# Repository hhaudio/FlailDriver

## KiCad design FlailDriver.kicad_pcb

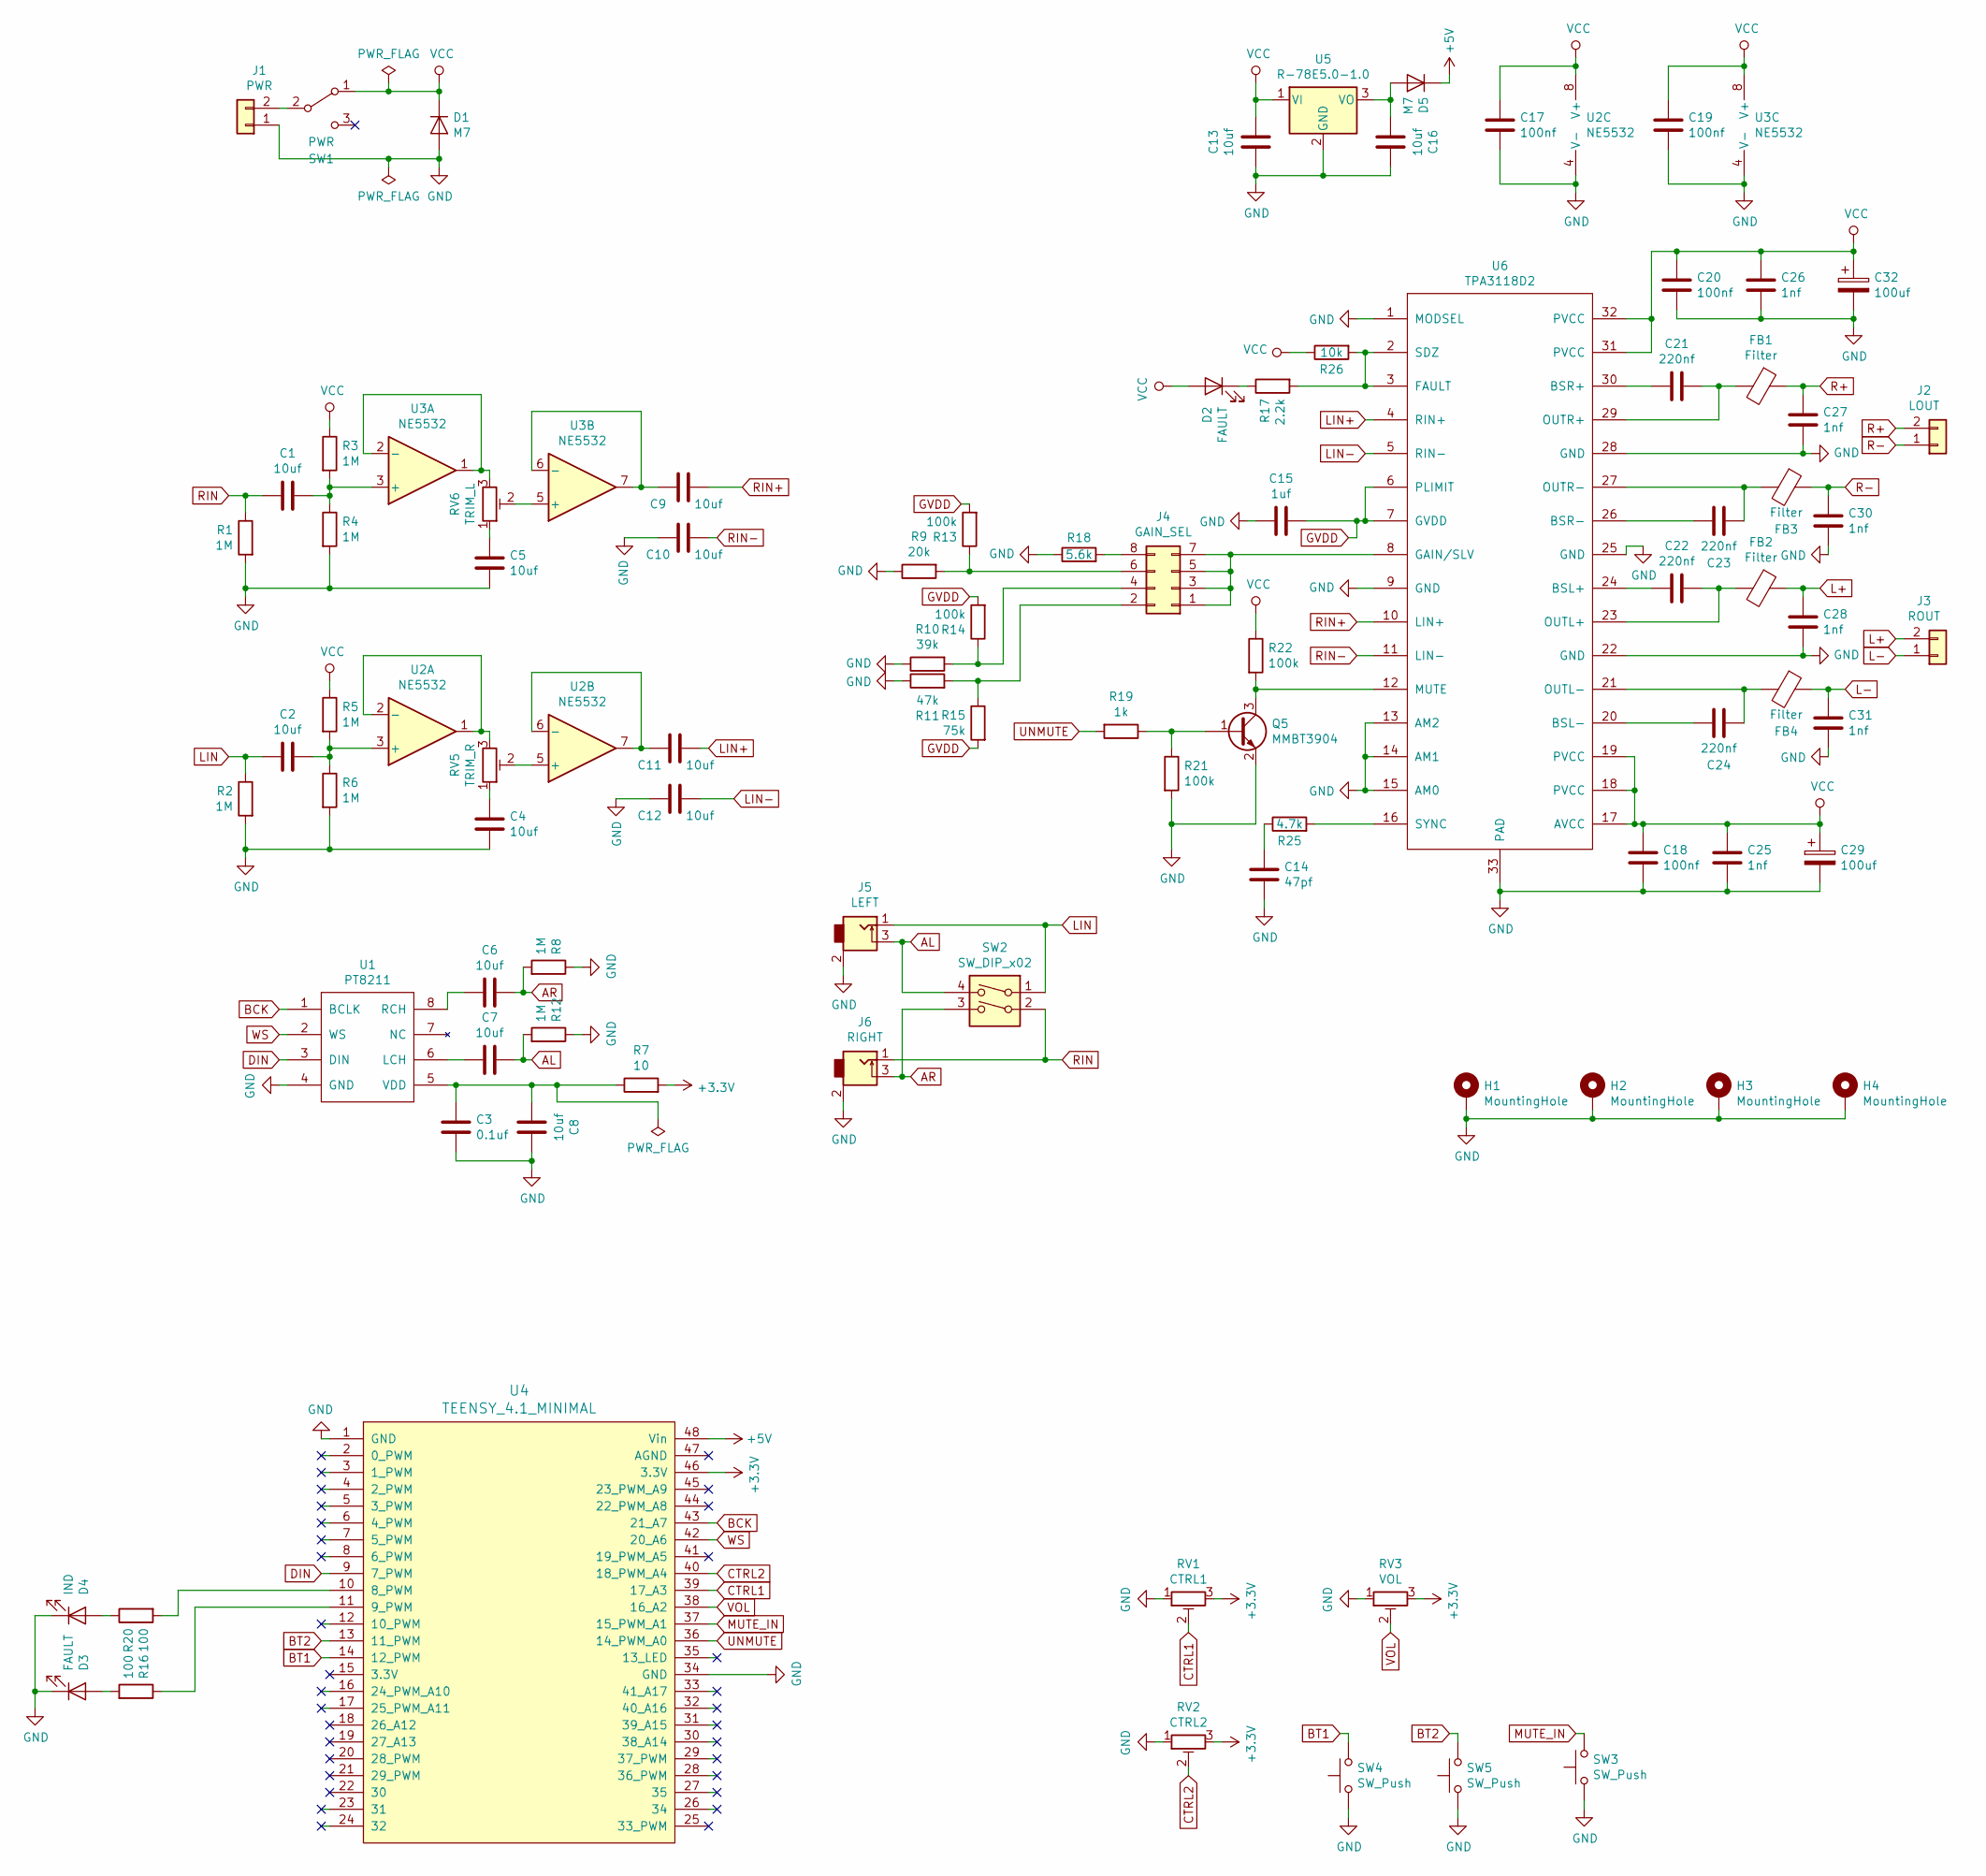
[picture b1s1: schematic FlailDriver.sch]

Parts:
C1, C2, C4, C5, C6, C7, C8, C9, C10, C11, C12, C13, C16: 10uf; C_0603_1608Metric_Pad1.05x0.95mm_HandSolder_HiddenRef; LCSC C96446
C3: 0.1uf; C_0603_1608Metric_Pad1.05x0.95mm_HandSolder_HiddenRef; LCSC C14663
C14: 47pf; C_0603_1608Metric_Pad1.05x0.95mm_HandSolder_HiddenRef; LCSC C1671
C15: 1uf; C_0603_1608Metric_Pad1.05x0.95mm_HandSolder_HiddenRef; LCSC C15849
C17, C18, C19, C20: 100nf; C_0603_1608Metric_Pad1.05x0.95mm_HandSolder_HiddenRef; LCSC C14663
C21, C22, C23, C24: 220nf; C_0603_1608Metric_Pad1.05x0.95mm_HandSolder_HiddenRef; LCSC C21120
C25, C26, C27, C28, C30, C31: 1nf; C_0603_1608Metric_Pad1.05x0.95mm_HandSolder_HiddenRef; LCSC C1588
C29, C32: 100uf; CP_Elec_6.3x7.7; LCSC C311622
D1, D5: M7; D_SMA; LCSC C95872
D2, D3: FAULT; LED_0805_2012Metric_Pad1.15x1.40mm_HandSolder; LCSC C84256
D4: IND; LED_0805_2012Metric_Pad1.15x1.40mm_HandSolder; LCSC C84256
FB1, FB2, FB3, FB4: Filter; L_1206_3216Metric_Pad1.42x1.75mm_HandSolder; LCSC C124704
H1, H2, H3, H4: MountingHole; M3_Plated
J1: PWR; Phoenix_Stacked_BackSilk_Centered_BoardEdge; LCSC C430323
J2: LOUT; Phoenix_Stacked_BackSilk_Centered_BoardEdge; LCSC C430323
J3: ROUT; Phoenix_Stacked_BackSilk_Centered_BoardEdge; LCSC C430323
J4: GAIN_SEL; PinHeader_2x04_P2.54mm_Vertical_SMD; LCSC C192300
J5: LEFT; EuroJack_MonoSW_THT_NOREF_SmallHoles_NoSilk
J6: RIGHT; EuroJack_MonoSW_THT_NOREF_SmallHoles_NoSilk
Q5: MMBT3904; SOT-23; LCSC C20526
R1, R2, R3, R4, R5, R6, R8, R12: 1M; R_0603_1608Metric_Pad1.05x0.95mm_HandSolder_HiddenRef; LCSC C22935
R7: 10; R_0603_1608Metric_Pad1.05x0.95mm_HandSolder_HiddenRef; LCSC C22859
R9: 20k; R_0603_1608Metric_Pad1.05x0.95mm_HandSolder_HiddenRef; LCSC C4184
R10: 39k; R_0603_1608Metric_Pad1.05x0.95mm_HandSolder_HiddenRef; LCSC C23153
R11: 47k; R_0603_1608Metric_Pad1.05x0.95mm_HandSolder_HiddenRef; LCSC C25819
R13, R14, R21, R22: 100k; R_0603_1608Metric_Pad1.05x0.95mm_HandSolder_HiddenRef; LCSC C25803
R15: 75k; R_0603_1608Metric_Pad1.05x0.95mm_HandSolder_HiddenRef; LCSC C23242
R16, R20: 100; R_0603_1608Metric_Pad1.05x0.95mm_HandSolder_HiddenRef; LCSC C22775
R17: 2.2k; R_0603_1608Metric_Pad1.05x0.95mm_HandSolder_HiddenRef; LCSC C4190
R18: 5.6k; R_0603_1608Metric_Pad1.05x0.95mm_HandSolder_HiddenRef; LCSC C23189
R19: 1k; R_0603_1608Metric_Pad1.05x0.95mm_HandSolder_HiddenRef; LCSC C21190
R25: 4.7k; R_0603_1608Metric_Pad1.05x0.95mm_HandSolder_HiddenRef; LCSC C23162
R26: 10k; R_0603_1608Metric_Pad1.05x0.95mm_HandSolder_HiddenRef; LCSC C25804
RV1: CTRL1; SMD_TRIM_JLC; LCSC C128550
RV2: CTRL2; SMD_TRIM_JLC; LCSC C128550
RV3: VOL; SMD_TRIM_JLC; LCSC C128550
RV5: TRIM_R; SMD_TRIM_JLC; LCSC C128550
RV6: TRIM_L; SMD_TRIM_JLC; LCSC C128550
SW1: PWR; JLC_SPDT_SLIDE_3A_C2887258; LCSC C2887258
SW2: SW_DIP_x02; JLC_SMD_DIP_SPSTx2_C40735; LCSC C40735
SW3, SW4, SW5: SW_Push; JLC_TactileSw_C318884; LCSC C318884
U1: PT8211; SOIC-8_3.9x4.9mm_P1.27mm; LCSC C5260468
U2, U3: NE5532; SO-8_3.9x4.9mm_P1.27mm; LCSC C7426
U4: TEENSY_4.1_MINIMAL; TEENSY_4.1_MINIMAL_DROP_IN
U5: R-78E5.0-1.0; TRACO_DCDC
U6: TPA3118D2; HTSSOP-32-1EP_6.1x11mm_P0.65mm_EP5.2x11mm_Mask4.11x4.36mm_T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; LCSC C46497

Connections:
+3V3: R7.2, RV1.3, RV2.3, RV3.3, U4.46 (3.3V)
+5V: D5.1 (K), U4.48 (Vin)
AL: C7.1, J5.3, R12.2, SW2.4
AR: C6.1, J6.3, R8.2, SW2.3
BCK: U1.1 (BCLK), U4.43 (21_A7)
BT1: SW4.2, U4.14 (12_PWM)
BT2: SW5.2, U4.13 (11_PWM)
CTRL1: RV1.2, U4.39 (17_A3)
CTRL2: RV2.2, U4.40 (18_PWM_A4)
DIN: U1.3 (DIN), U4.9 (7_PWM)
GND: C3.2, C4.2, C5.2, C8.2, C10.2, C12.2, C13.2, C14.2, C15.2, C16.2, C17.2, C18.2, C19.2, C20.2, C25.2, C26.2, C27.2, C28.2, C29.2, C30.2, C31.2, C32.2, D1.2 (A), D3.1 (K), D4.1 (K), H1.1, H2.1, H3.1, H4.1, J1.1, J5.2, J6.2, Q5.2 (E), R1.2, R2.2, R4.2, R6.2, R8.1, R9.1, R10.1, R11.1, R12.1, R18.1, R21.2, RV1.1, RV2.1, RV3.1, SW3.1, SW4.1, SW5.1, U1.4 (GND), U2.4 (V-), U3.4 (V-), U4.1 (GND), U4.34 (GND), U5.2 (GND), U6.1 (MODSEL), U6.9 (GND), U6.13 (AM2), U6.14 (AM1), U6.15 (AM0), U6.22 (GND), U6.25 (GND), U6.28 (GND), U6.33 (PAD)
GVDD: C15.1, R13.2, R14.2, R15.2, U6.6 (PLIMIT), U6.7 (GVDD)
L+: C28.1, FB2.1, J3.2
L-: C31.1, FB4.1, J3.1
LIN: C2.2, J5.1, R2.1, SW2.1
LIN+: C11.1, U6.4 (RIN+)
LIN-: C12.1, U6.5 (RIN-)
MUTE_IN: SW3.2, U4.37 (15_PWM_A1)
unnamed: C1.1, R3.2, R4.1, U3.3 (+)
unnamed: C2.1, R5.2, R6.1, U2.3 (+)
unnamed: C3.1, C8.1, R7.1, U1.5 (VDD)
unnamed: C4.1, RV5.1
unnamed: C5.1, RV6.1
unnamed: C6.2, U1.8 (RCH)
unnamed: C7.2, U1.6 (LCH)
unnamed: C9.2, U3.6 (-), U3.7
unnamed: C11.2, U2.6 (-), U2.7
unnamed: C14.1, R25.1
unnamed: C16.1, D5.2 (A), U5.3 (VO)
unnamed: C21.1, FB1.2, U6.29 (OUTR+)
unnamed: C21.2, U6.30 (BSR+)
unnamed: C22.1, FB2.2, U6.23 (OUTL+)
unnamed: C22.2, U6.24 (BSL+)
unnamed: C23.1, U6.26 (BSR-)
unnamed: C23.2, FB3.2, U6.27 (OUTR-)
unnamed: C24.1, U6.20 (BSL-)
unnamed: C24.2, FB4.2, U6.21 (OUTL-)
unnamed: D2.1 (K), R17.1
unnamed: D3.2 (A), R16.2
unnamed: D4.2 (A), R20.1
unnamed: J1.2, SW1.2 (B)
unnamed: J4.1, J4.3, J4.5, J4.7, U6.8 (GAIN/SLV)
unnamed: J4.2, R11.2, R15.1
unnamed: J4.4, R10.2, R14.1
unnamed: J4.6, R9.2, R13.1
unnamed: J4.8, R18.2
unnamed: Q5.1 (B), R19.1, R21.1
unnamed: Q5.3 (C), R22.2, U6.12 (MUTE)
unnamed: R16.1, U4.11 (9_PWM)
unnamed: R17.2, R26.2, U6.2 (SDZ), U6.3 (FAULT)
unnamed: R20.2, U4.10 (8_PWM)
unnamed: R25.2, U6.16 (SYNC)
unnamed: RV5.2, U2.5 (+)
unnamed: RV5.3, U2.1, U2.2 (-)
unnamed: RV6.2, U3.5 (+)
unnamed: RV6.3, U3.1, U3.2 (-)
R+: C27.1, FB1.1, J2.2
R-: C30.1, FB3.1, J2.1
RIN: C1.2, J6.1, R1.1, SW2.2
RIN+: C9.1, U6.10 (LIN+)
RIN-: C10.1, U6.11 (LIN-)
UNMUTE: R19.2, U4.36 (14_PWM_A0)
VCC: C13.1, C17.1, C18.1, C19.1, C20.1, C25.1, C26.1, C29.1, C32.1, D1.1 (K), D2.2 (A), R3.1, R5.1, R22.1, R26.1, SW1.1 (A), U2.8 (V+), U3.8 (V+), U5.1 (VI), U6.17 (AVCC), U6.18 (PVCC), U6.19 (PVCC), U6.31 (PVCC), U6.32 (PVCC)
VOL: RV3.2, U4.38 (16_A2)
WS: U1.2 (WS), U4.42 (20_A6)

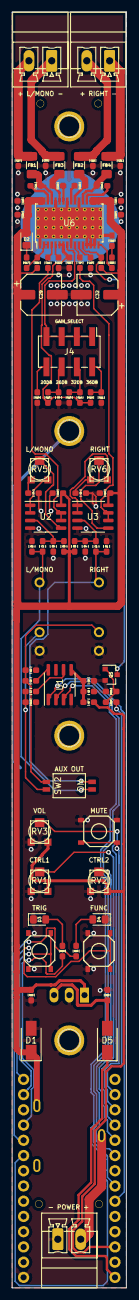
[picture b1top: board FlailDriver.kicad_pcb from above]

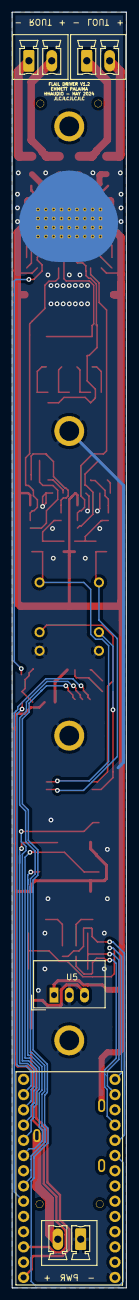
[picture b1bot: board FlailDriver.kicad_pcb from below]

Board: 2 copper layers, 19.0 x 212.7 mm, 92 parts (2 on the bottom side), 65 nets.

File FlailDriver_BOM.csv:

Comment,Designator,Footprint,LCSC
"10uf","C1,C2,C4,C5,C6,C7,C8,C9,C10,C11,C12,C13,C16","Capacitor_SMD:C_0603_1608Metric_Pad1.05x0.95mm_HandSolder_HiddenRef","C96446"
"47pf","C14","Capacitor_SMD:C_0603_1608Metric_Pad1.05x0.95mm_HandSolder_HiddenRef","C1671"
"1uf","C15","Capacitor_SMD:C_0603_1608Metric_Pad1.05x0.95mm_HandSolder_HiddenRef","C15849"
"100nf","C17,C18,C19,C20","Capacitor_SMD:C_0603_1608Metric_Pad1.05x0.95mm_HandSolder_HiddenRef","C14663"
"220nf","C21,C22,C23,C24","Capacitor_SMD:C_0603_1608Metric_Pad1.05x0.95mm_HandSolder_HiddenRef","C21120"
"1nf","C25,C26,C27,C28,C30,C31","Capacitor_SMD:C_0603_1608Metric_Pad1.05x0.95mm_HandSolder_HiddenRef","C1588"
"100uf","C29,C32","Capacitor_SMD:CP_Elec_6.3x7.7","C311622"
"0.1uf","C3","Capacitor_SMD:C_0603_1608Metric_Pad1.05x0.95mm_HandSolder_HiddenRef","C14663"
"M7","D1,D5","Diode_SMD:D_SMA","C95872"
"FAULT","D2,D3","LED_SMD:LED_0805_2012Metric_Pad1.15x1.40mm_HandSolder","C84256"
"IND","D4","LED_SMD:LED_0805_2012Metric_Pad1.15x1.40mm_HandSolder","C84256"
"Filter","FB1,FB2,FB3,FB4","Inductor_SMD:L_1206_3216Metric_Pad1.42x1.75mm_HandSolder","C124704"
"MountingHole","H1,H2,H3,H4","HammerheadAudio:M3_Plated",""
"PWR","J1","HammerheadAudio:Phoenix_Stacked_BackSilk_Centered_BoardEdge","C430323"
"LOUT","J2","HammerheadAudio:Phoenix_Stacked_BackSilk_Centered_BoardEdge","C430323"
"ROUT","J3","HammerheadAudio:Phoenix_Stacked_BackSilk_Centered_BoardEdge","C430323"
"GAIN_SEL","J4","Connector_PinHeader_2.54mm:PinHeader_2x04_P2.54mm_Vertical_SMD","C192300"
"LEFT","J5","HammerheadAudio:EuroJack_MonoSW_THT_NOREF_SmallHoles_NoSilk",""
"RIGHT","J6","HammerheadAudio:EuroJack_MonoSW_THT_NOREF_SmallHoles_NoSilk",""
"MMBT3904","Q5","Package_TO_SOT_SMD:SOT-23","C20526"
"39k","R10","Resistor_SMD:R_0603_1608Metric_Pad1.05x0.95mm_HandSolder_HiddenRef","C23153"
"47k","R11","Resistor_SMD:R_0603_1608Metric_Pad1.05x0.95mm_HandSolder_HiddenRef","C25819"
"75k","R15","Resistor_SMD:R_0603_1608Metric_Pad1.05x0.95mm_HandSolder_HiddenRef","C23242"
"100","R16,R20","Resistor_SMD:R_0603_1608Metric_Pad1.05x0.95mm_HandSolder_HiddenRef","C22775"
"2.2k","R17","Resistor_SMD:R_0603_1608Metric_Pad1.05x0.95mm_HandSolder_HiddenRef","C4190"
"5.6k","R18","Resistor_SMD:R_0603_1608Metric_Pad1.05x0.95mm_HandSolder_HiddenRef","C23189"
"1k","R19","Resistor_SMD:R_0603_1608Metric_Pad1.05x0.95mm_HandSolder_HiddenRef","C21190"
"100k","R13,R14,R21,R22","Resistor_SMD:R_0603_1608Metric_Pad1.05x0.95mm_HandSolder_HiddenRef","C25803"
"4.7k","R25","Resistor_SMD:R_0603_1608Metric_Pad1.05x0.95mm_HandSolder_HiddenRef","C23162"
"10k","R26","Resistor_SMD:R_0603_1608Metric_Pad1.05x0.95mm_HandSolder_HiddenRef","C25804"
"1M","R1,R2,R3,R4,R5,R6,R8,R12","Resistor_SMD:R_0603_1608Metric_Pad1.05x0.95mm_HandSolder_HiddenRef","C22935"
"10","R7","Resistor_SMD:R_0603_1608Metric_Pad1.05x0.95mm_HandSolder_HiddenRef","C22859"
"20k","R9","Resistor_SMD:R_0603_1608Metric_Pad1.05x0.95mm_HandSolder_HiddenRef","C4184"
"CTRL1","RV1","Crossley_Footprints:SMD_TRIM_JLC","C128550"
"CTRL2","RV2","Crossley_Footprints:SMD_TRIM_JLC","C128550"
"VOL","RV3","Crossley_Footprints:SMD_TRIM_JLC","C128550"
"TRIM_R","RV5","Crossley_Footprints:SMD_TRIM_JLC","C128550"
"TRIM_L","RV6","Crossley_Footprints:SMD_TRIM_JLC","C128550"
"PWR","SW1","HammerheadAudio:JLC_SPDT_SLIDE_3A_C2887258","C2887258"
"SW_Push","SW3,SW4,SW5","HammerheadAudio:JLC_TactileSw_C318884","C318884"
"PT8211","U1","Package_SO:SOIC-8_3.9x4.9mm_P1.27mm","C5260468"
"NE5532","U2,U3","Package_SO:SO-8_3.9x4.9mm_P1.27mm","C7426"
"TEENSY_4.1_MINIMAL","U4","MeowWolf_Templates:TEENSY_4.1_MINIMAL_DROP_IN",""
"L7805CD2T-TR","U5","Package_TO_SOT_SMD:TO-263-2","C15077"
"TPA3118D2","U6","Package_SO:HTSSOP-32-1EP_6.1x11mm_P0.65mm_EP5.2x11mm_Mask4.11x4.36mm_ThermalVias","C46497"

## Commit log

2023-05-13 schematic, start on layout
2023-05-15 commit before routing traces
2023-05-15 layout progress
2023-05-16 layout finished
2024-05-27 switching 5V regulator
2024-05-29 newreg
2024-06-12 bak:
